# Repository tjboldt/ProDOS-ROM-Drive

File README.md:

# v4.0
This is a new revision of the hardware, incompatible with previous firmware and drive image before v3. If you have a v2.5 board, see the v2.5 tag [here](https://github.com/tjboldt/ProDOS-ROM-Drive/tree/v2.5). Note that all of v2.1, v2.5 and v3.0 have a small design mistake that didn't properly buffer the data bus the way it was intended in the original v1.0 version. This has been fixed for v4.0.

# ProDOS ROM-Drive
This is a peripheral card for the Apple ][ series computers that acts as a read-only solid state disk drive (SSD) all in EPROM. Although it won't run DOS, it is fully ProDOS compatible and will appear as a read-only hard drive even when booting from another drive. It holds 1024 KB of disk data with the 256 byte firmware stored in block 0001 where the SOS boot loader normally resides. The drive boots ProDOS and into BASIC in under 1.5 seconds. 

You can order blank circuit boards from [PCBWay](https://www.pcbway.com/project/shareproject/ProDOS_ROM_Drive_v4_4fe0794f.html) or upload the provided gerber and drill files to any PCB manufacturer.

## History

My first Apple computer was an Apple //e that my brother bought in early 1984. Countless hours were spent playing games which developed my interest in building games. This also led to the creation of various utilities to help organize disks or just to see what could be done while programming.

As time passed, I obtained other machines far more powerful and eventually my once loved Apple IIe got used less and less. I did still pull it out of storage every few months to play some classic games or see what I could accomplish with greater programming skills. The problem was connecting up disk drives, looking for disks and hoping that the disks still worked. To make life simpler, I decided I needed to come up with some way to permanently store the files inside the computer without needing to plug in anything but the power and video connectors. This is where the idea for a solid-state drive began.

In the summer of 1998 I did some research in my own Apple II library for information on building peripheral cards. I drew up some designs in September 1998 and started building a prototype on a solderless breadboard with the wires jumpered over from a dead parallel card which I had cut the traces on. The rough idea at the time was to have two EPROMs. One would hold the 256 bytes of code in the $Cs00 - $CsFF space (where s is the slot number) and the second EPROM would get accessed through the 16 byte port space for the slot. To access more than 16 bytes, I would have a couple latch chips where you could program in the address of the disk EPROM and then read it one byte at a time through the ports. Originally I was going to make my own modified version of DOS 3.3 but before I got too far, David Wilson from Australia convinced me that it was much easier to build it for ProDOS since it supported many types of drives natively.

By November 1998 I had a prototype on the solderless breadboard that could read data from the EPROM but it had no driver code, didn't boot and was very unreliable. In December I managed to have the two EPROM based system running but it would fail to boot about 80% of the time with various read errors. Shortening the length of wires, cleaning up the layout and a new design helped but it was still unreliable. I finally gave up on the second design but as it turns out, it could have been fixed quite easily.

By mid-May of 1999 I finally got around to building a third design. This time I reduced the chip count and made the firmware for the drive reside in the top two blocks of the virtual disk EPROM. It still was somewhat unreliable in slot one but it was progressively worse as it was placed into higher slot numbers. By slot seven the card was completely unuseable. I then discovered that adding a 104 ceramic capacitor to each chip made the problem disappear. It was suddenly fully reliable.

To build actual circuit boards, I tried making some by hand with marker, etching solution and copper on fibreglass boards but this proved to be far too difficult. I then learned the wonders of gerber files which can be created with a variety of PCB layout software. The files were emailed to a company in Alberta, Canada and three days later in July of 1999 I received a batch of 10 blank boards. These boards did not have the familiar green board look to them, nor were they pre-cut. I had to cut and file them to fit an Apple II slot by hand. Back then it was prohitively expensive for a young hobbiest to make less than 20 or 30 boards with the full solder-masking process due to the set-up fees.

In 2019, I decided to revisit the original design as I was disappointed that the original didn't have a solder mask and was rather large for what it was. I got the board much smaller but in the process of translating my two decade old hand written notes, I made a mistake on one control line. To actually call this project finished, I had to make another revision. I also noticed the revised board was slightly larger than a credit card so I worked for a couple weeks to optimize the lines and squeeze the two-layer board down to 3.375" x 2.125". (Note that references above to first, second and third design are all the solderless breadboard prototypes leading up to the 1.0 circuit board printed in 1999, 2.0 was never made, 2.1 is the board with the error patched with a jumper wire and 2.2 through 2.4 were never made).

In 2021, the first ever issue was opened on the project requesting that the firmware be relocatable. I let that issue sit for a few months and then Ralle Palaveev supplied some relocatable firmware as a patch. I quickly realized that this could be placed into the second block on the drive normally reserved for SOS bootloader for the Apple ///, essentially allowing the full EPROM to be used for the drive. I disassembed Ralle's patch, merged it into the existing source code and made a few updates to save a few bytes and add clarity. This change required some differences in wiring for the firmware addressing on the card. The final revision 4.0 was made in 2022 to fix the data buffer wiring but was otherwise the same as 3.0.

## Notes
I used to use Ciderpress to copy files onto the drive image but now use my own cross-platform command line tool [ProDOS-Utilities](https://github.com/tjboldt/ProDOS-Utilities) and sometimes make modifications to the image live via an Apple II emulator. I then burn the file to a 27C801 EPROM with a GQ-4x4 USB Programmer. Do NOT overwrite block 0001 in the image as it contains the firmware for the card.

If you're planning on designing you own card, I highly recommend reading "Interfacing & Digital Experiments with your Apple" by Charles J. Engelisher and Apple's "Apple II Reference Manual" as well as "ProDOS Technical Reference Manual" if you want to build a drive. You also need an EPROM programmer, some chips and a prototyping board. My designs used simple logic gates to decode addresses but if you want to reduce chip count, you'll also need a PAL/GAL logic programmer (which some EPROM programmers can do).

## Website
Official website is [apple2.ca](http://apple2.ca/).

## Purchasing a ProDOS ROM-Drive
I generally no longer sell these cards but you can buy them online from [Laser](https://www.laser.com/product_info.php/item/ProDOS_ROM_Drive-Apple_II_ProDOS_bootable_1MB_read-only_drive/cPath/288_292/products_id/1984) and other retailers.

## Other links
- [Thread about building the card](https://tinkerdifferent.com/threads/building-tjboldts-prodos-rom-drive-for-apple.1249/)
- [Article about the card](https://www.callapple.org/hardware/prodos-rom-drive-version-3/)
- [Alternate version with fewer chips](https://www.ebay.com/itm/374004896438)

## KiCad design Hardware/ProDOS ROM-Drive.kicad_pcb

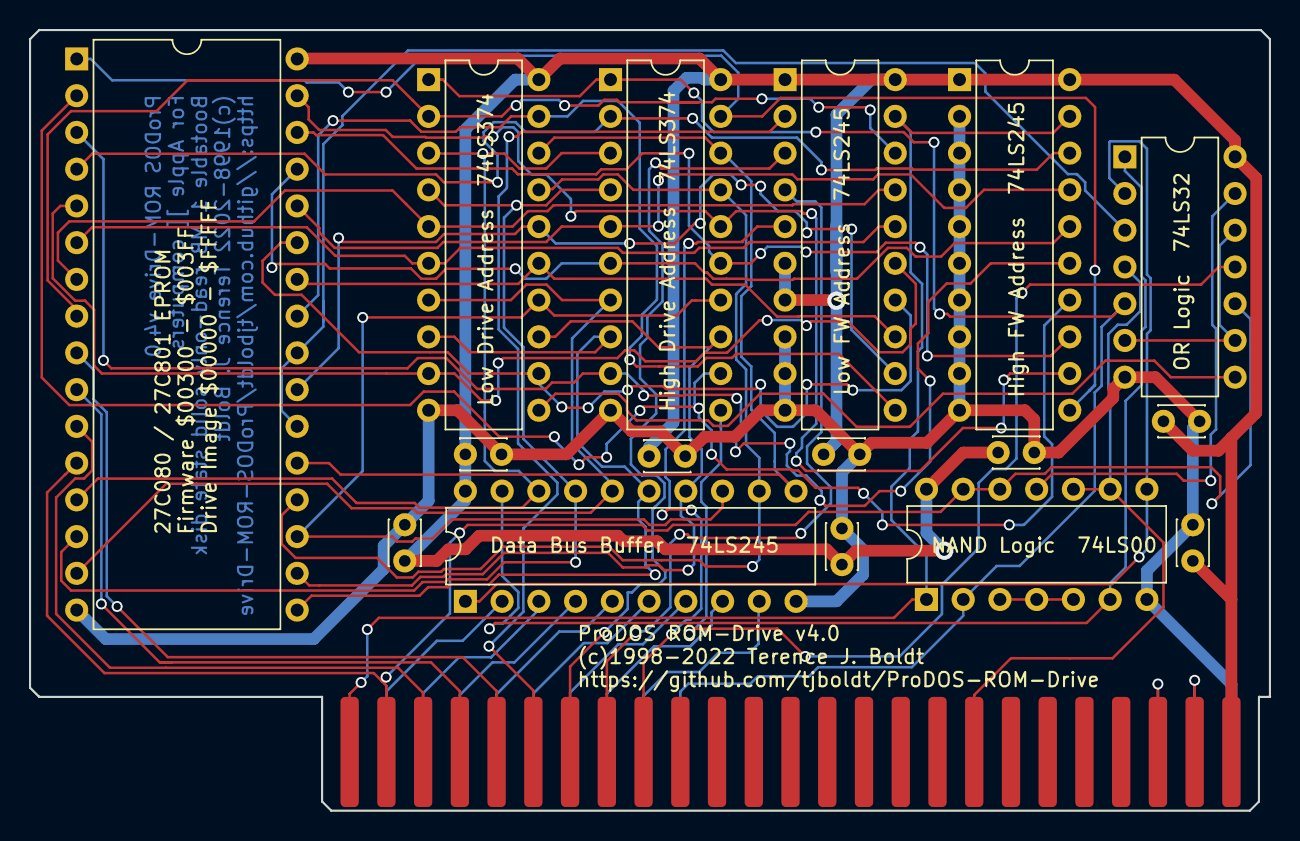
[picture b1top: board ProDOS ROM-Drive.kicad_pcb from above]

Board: 2 copper layers, 85.7 x 54.0 mm, 17 parts (0 on the bottom side), 55 nets.

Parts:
C1, C2, C3, C4, C5, C6, C7, C8: 0.1µF; C_Disc_D3.0mm_W2.0mm_P2.50mm
DataBuffer1: 74LS245; DIP-20_W7.62mm
EPROM1: 27C080; DIP-32_W15.24mm
HiAddrBuffer1: 74LS245; DIP-20_W7.62mm
HiAddrLatch1: 74LS374; DIP-20_W7.62mm
J1: Apple II Expansion Slot; Apple II Expansion Edge Connector
LowAddrBuffer1: 74LS245; DIP-20_W7.62mm
LowAddrLatch1: 74LS374; DIP-20_W7.62mm
U1: 74LS00; DIP-14_W7.62mm
U2: 74LS32; DIP-14_W7.62mm

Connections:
+5V: C1.1, C2.1, C3.1, C4.1, C5.1, C6.1, C7.1, C8.1, DataBuffer1.20 (VCC), EPROM1.32 (VCC), HiAddrBuffer1.1 (A->B), HiAddrBuffer1.20 (VCC), HiAddrLatch1.20 (VCC), J1.25 (GND), LowAddrBuffer1.1 (A->B), LowAddrBuffer1.6 (A4), LowAddrBuffer1.7 (A5), LowAddrBuffer1.20 (VCC), LowAddrLatch1.20 (VCC), U1.14 (VCC), U2.14 (VCC)
/A0: EPROM1.12 (A0), J1.2, U1.12, U1.13, U2.10
/A1: EPROM1.11 (A1), J1.3
/A2: EPROM1.10 (A2), J1.4
/A3: EPROM1.9 (A3), J1.5
/A4: J1.6, LowAddrBuffer1.2 (A0)
/A5: J1.7, LowAddrBuffer1.3 (A1)
/A6: J1.8, LowAddrBuffer1.4 (A2)
/A7: J1.9, LowAddrBuffer1.5 (A3)
/CA4: EPROM1.8 (A4), LowAddrBuffer1.18 (B0), LowAddrLatch1.2 (O0)
/CA5: EPROM1.7 (A5), LowAddrBuffer1.17 (B1), LowAddrLatch1.5 (O1)
/CA6: EPROM1.6 (A6), LowAddrBuffer1.16 (B2), LowAddrLatch1.6 (O2)
/CA7: EPROM1.5 (A7), LowAddrBuffer1.15 (B3), LowAddrLatch1.9 (O3)
/CA8: EPROM1.27 (A8), LowAddrBuffer1.14 (B4), LowAddrLatch1.12 (O4)
/CA9: EPROM1.26 (A9), LowAddrBuffer1.13 (B5), LowAddrLatch1.15 (O5)
/CA10: EPROM1.23 (A10), LowAddrBuffer1.12 (B6), LowAddrLatch1.16 (O6)
/CA11: EPROM1.25 (A11), LowAddrBuffer1.11 (B7), LowAddrLatch1.19 (O7)
/CA12: EPROM1.4 (A12), HiAddrBuffer1.18 (B0), HiAddrLatch1.2 (O0)
/CA13: EPROM1.28 (A13), HiAddrBuffer1.17 (B1), HiAddrLatch1.5 (O1)
/CA14: EPROM1.29 (A14), HiAddrBuffer1.16 (B2), HiAddrLatch1.6 (O2)
/CA15: EPROM1.3 (A15), HiAddrBuffer1.15 (B3), HiAddrLatch1.9 (O3)
/CA16: EPROM1.2 (A16), HiAddrBuffer1.14 (B4), HiAddrLatch1.12 (O4)
/CA17: EPROM1.30 (A17), HiAddrBuffer1.13 (B5), HiAddrLatch1.15 (O5)
/CA18: EPROM1.31 (A18), HiAddrBuffer1.12 (B6), HiAddrLatch1.16 (O6)
/CA19: EPROM1.1 (A19), HiAddrBuffer1.11 (B7), HiAddrLatch1.19 (O7)
/CD0: DataBuffer1.18 (B0), EPROM1.13 (D0), HiAddrLatch1.3 (D0), LowAddrLatch1.3 (D0)
/CD1: DataBuffer1.17 (B1), EPROM1.14 (D1), HiAddrLatch1.4 (D1), LowAddrLatch1.4 (D1)
/CD2: DataBuffer1.16 (B2), EPROM1.15 (D2), HiAddrLatch1.7 (D2), LowAddrLatch1.7 (D2)
/CD3: DataBuffer1.15 (B3), EPROM1.17 (D3), HiAddrLatch1.8 (D3), LowAddrLatch1.8 (D3)
/CD4: DataBuffer1.14 (B4), EPROM1.18 (D4), HiAddrLatch1.13 (D4), LowAddrLatch1.13 (D4)
/CD5: DataBuffer1.13 (B5), EPROM1.19 (D5), HiAddrLatch1.14 (D5), LowAddrLatch1.14 (D5)
/CD6: DataBuffer1.12 (B6), EPROM1.20 (D6), HiAddrLatch1.17 (D6), LowAddrLatch1.17 (D6)
/CD7: DataBuffer1.11 (B7), EPROM1.21 (D7), HiAddrLatch1.18 (D7), LowAddrLatch1.18 (D7)
/D0: DataBuffer1.2 (A0), J1.49
/D1: DataBuffer1.3 (A1), J1.48
/D2: DataBuffer1.4 (A2), J1.47
/D3: DataBuffer1.5 (A3), J1.46
/D4: DataBuffer1.6 (A4), J1.45
/D5: DataBuffer1.7 (A5), J1.44
/D6: DataBuffer1.8 (A6), J1.43
/D7: DataBuffer1.9 (A7), J1.42
/DMA: J1.24, J1.27
/INT: J1.23, J1.28
/R/~W: J1.18, U1.9, U1.10, U2.4
/~A0: U1.11, U2.13
/~DEVICE SELECT: HiAddrLatch1.1 (OE), J1.41, LowAddrLatch1.1 (OE), U1.2, U2.5
/~HIGH LATCH ENABLE: HiAddrLatch1.11 (Cp), U2.11
/~IO SELECT: HiAddrBuffer1.19 (CE), J1.1, LowAddrBuffer1.19 (CE), U1.1
/~IO SELECT AND ~DEVICE SELECT: DataBuffer1.19 (CE), U1.6, U2.1
/~LOW LATCH ENABLE: LowAddrLatch1.11 (Cp), U2.8
/~ROM ENABLE: EPROM1.22 (~CE), EPROM1.24 (~OE), U2.3
/~R/W: DataBuffer1.1 (A->B), U1.8, U2.2
GND: C1.2, C2.2, C3.2, C4.2, C5.2, C6.2, C7.2, C8.2, DataBuffer1.10 (GND), EPROM1.16 (GND), HiAddrBuffer1.2 (A0), HiAddrBuffer1.3 (A1), HiAddrBuffer1.4 (A2), HiAddrBuffer1.5 (A3), HiAddrBuffer1.6 (A4), HiAddrBuffer1.7 (A5), HiAddrBuffer1.8 (A6), HiAddrBuffer1.9 (A7), HiAddrBuffer1.10 (GND), HiAddrLatch1.10 (GND), J1.26 (+5V), LowAddrBuffer1.8 (A6), LowAddrBuffer1.9 (A7), LowAddrBuffer1.10 (GND), LowAddrLatch1.10 (GND), U1.7 (GND), U2.7 (GND)
unnamed: U1.3, U1.4, U1.5
unnamed: U2.6, U2.9, U2.12

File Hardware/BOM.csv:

Part,Quantity,Supplier Part #,Supplier
74LS32,1,595-SN74LS32N,Mouser
74LS00,1,595-SN74LS00N,Mouser
74LS245,3,595-SN74LS245N,Mouser
74LS374,2,595-SN74LS374N,Mouser
0.1µF Capacitor,8,594-K104K15X7RF5TH5,Mouser
14 Pin DIP Socket,2,571-1-2199298-3,Mouser
20 Pin DIP Socket,5,571-1-2199298-6,Mouser
32 Pin DIP Socket,1,571-1-2199300-2,Mouser
27C080 or 27C801,1,Obsolete,eBay

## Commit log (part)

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2019-05-13 Initial push to git
2019-05-13 Adding blank ProDOS drive with firmware assembled in top 2KB
2019-05-13 Create LICENSE
2019-05-13 Removed duplicate license
2019-05-14 Made image of board smaller
2019-10-20 Add missing schematic files as they were part of revision 2.2 where PCB was 2.5
2020-12-01 Update assembler code to work with modern version of cc65 tools
2020-12-01 Update assembly instructions
2021-04-01 Remove unnecessary code
2021-04-01 Update binary and drive image
2021-12-08 Add files via upload
    Firmware with relative code.
2021-12-10 Move firmware patch to Firmware directory
2021-12-10 Update hardware to use block 0001 for firmware
2021-12-12 Update firmware source to be relocatable
2021-12-12 Update blank drive image
2021-12-12 Update firmware listing
2021-12-21 Add files via upload
    An updated patch with optimmized code.
2021-12-21 Add files via upload
    An updated patched firmware with optimized code.
2021-12-22 Fixed firmware for v3 board
2021-12-23 Fix text display due to change in Y offset
2021-12-24 Fix text
2022-02-24 Rename files without version
2022-02-24 Ignore KiCAD 6 backups
2022-02-24 Update to KiCAD 6
2022-03-19 Update schematic and fix data bus lines
2022-03-19 Updated gerber files to be compatible with PCBWay
2022-03-19 Update firmware date and version
2022-07-12 Update driver to not need JSR $FF58 on entry
    Save and restore zero page values
2022-11-02 Add ESC to skip boot to next slot
2022-11-06 Add boot slot 1 - 7 in startup menu
2023-11-06 Add BOM, closes #19
2026-02-17 Refactor variable names and comments for clarity in Firmware.asm
2026-02-21 Feedback from PR comments and another read-through
    Update variable name and copyright year in firmware
2026-02-21 Forgot the copyright message in the warning block
    Update copyright year to 2026
2026-02-22 Rename both writeIo ports the same way
2026-02-26 Assemble latest firmare and update copyright
2026-02-26 Add script to burn EPROM

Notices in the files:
Hardware/ProDOS ROM-Drive.kicad_pcb:
(c)1998-2022 Terence J. Boldt
